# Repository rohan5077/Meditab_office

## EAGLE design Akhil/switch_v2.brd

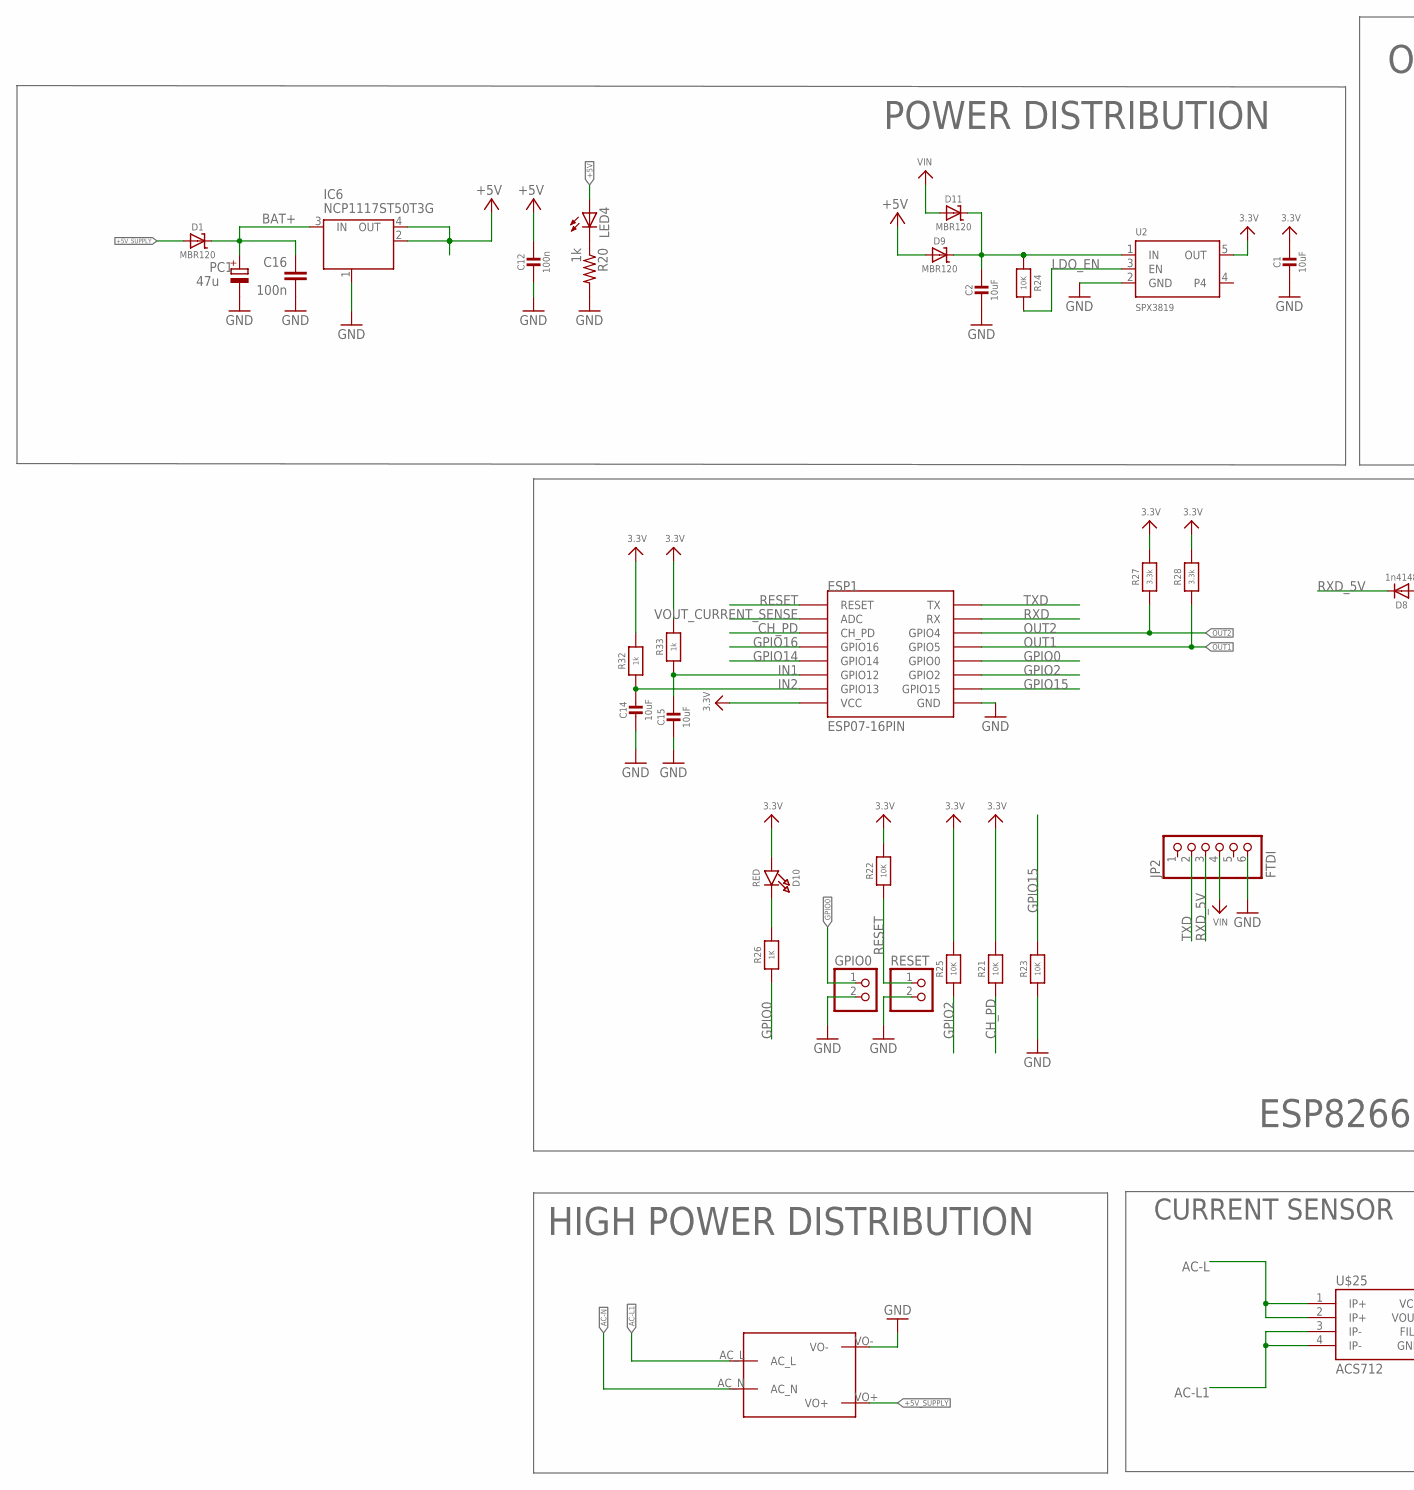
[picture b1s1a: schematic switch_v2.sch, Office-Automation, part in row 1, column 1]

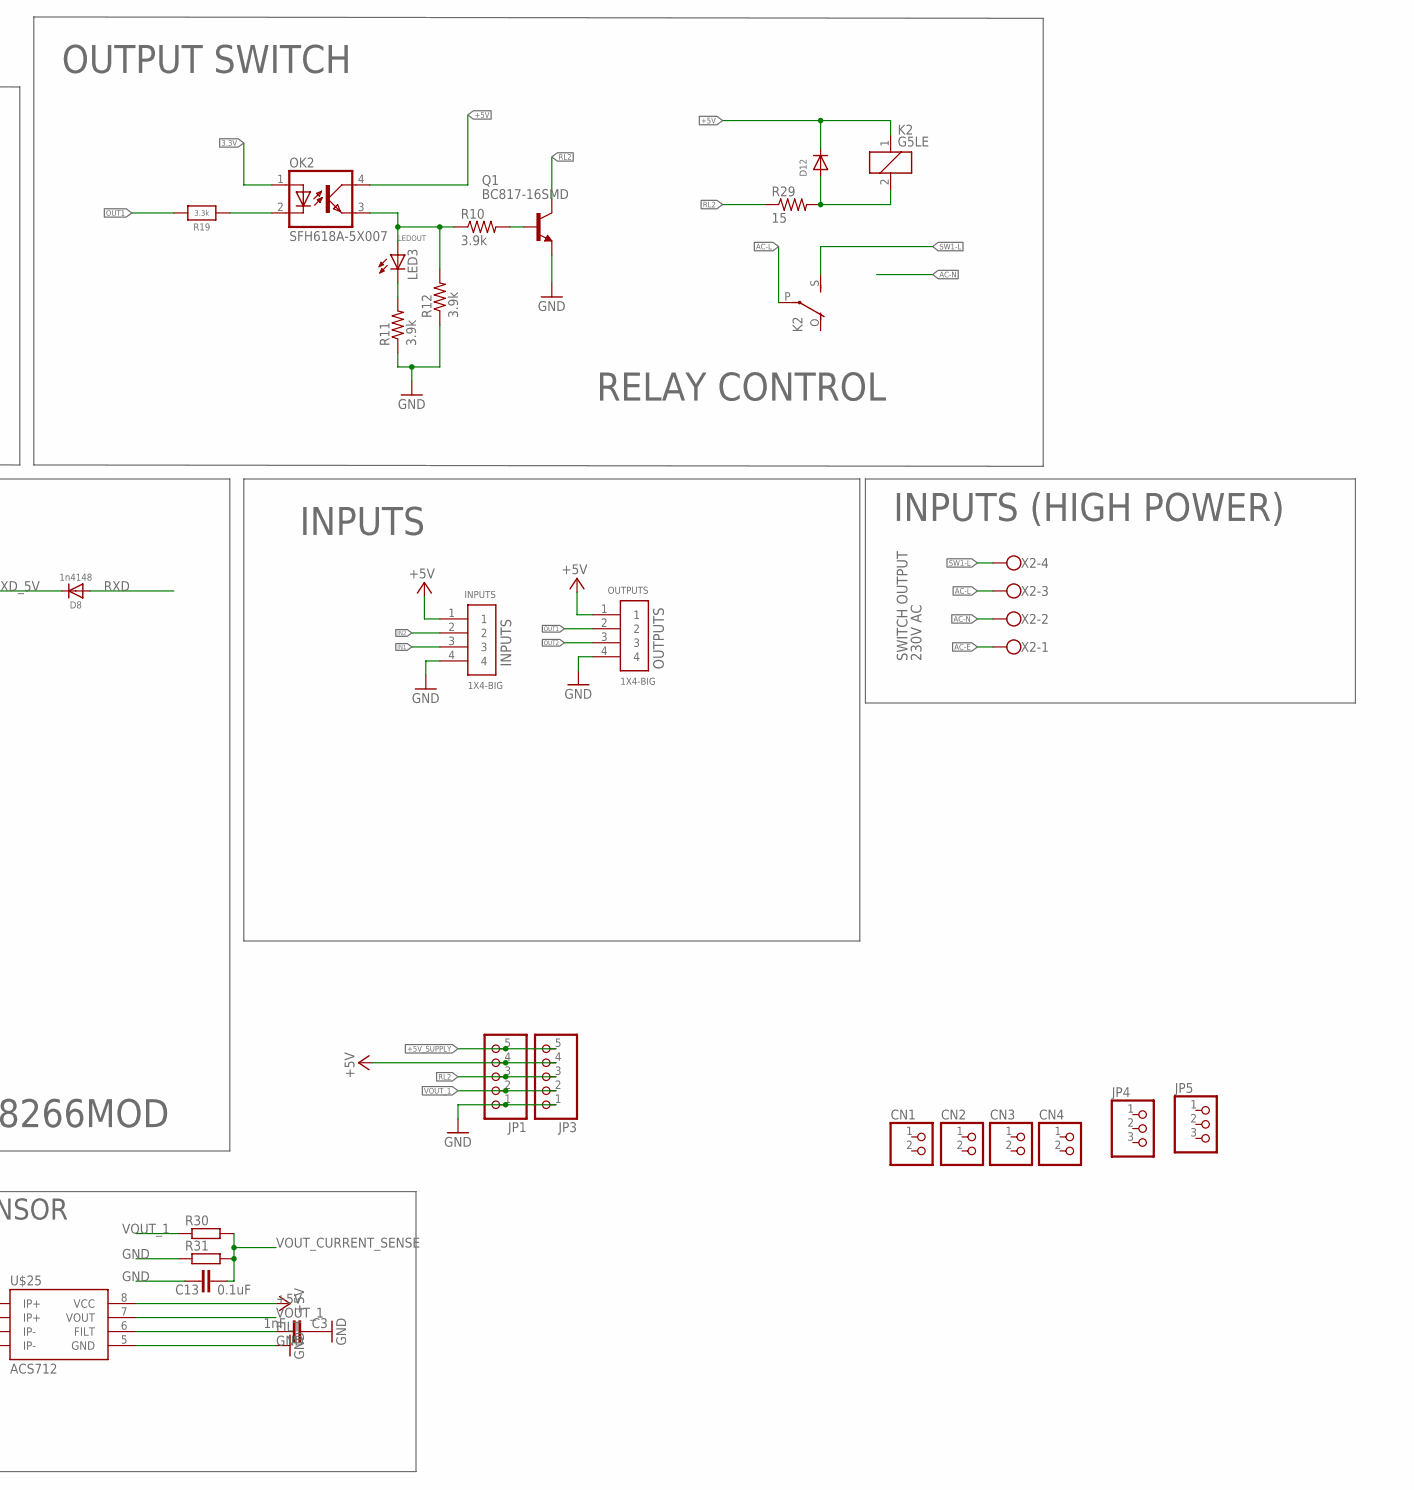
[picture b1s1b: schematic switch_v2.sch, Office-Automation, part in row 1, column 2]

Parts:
C1, C2, C14, C15: 10uF; _0603
C3: 1nF; C0603-ROUND
C12: 100n; _0603
C13: 0.1uF; C0603-ROUND
C16: 100n; C0603-ROUND
CN1, CN2, CN3, CN4: PINHD-1X2; 1X02
D1, D9, D11: MBR120; SOD-123
D8: 1n4148; SOD-323
D10: RED; CHIPLED_0603_NOOUTLINE
D12: DIODESOD-523; SOD-523
ESP1: ESP07-16PIN
GPIO0: PINHD-1X2; 1X02
IC6: NCP1117ST50T3G; SOT223
INPUTS: 1X4-BIG; 1X04-BIG
JP1, JP3: PINHD-1X5; 1X05
JP2: FTDI; 1X06_ROUND_70
JP4, JP5: PINHD-1X3; 1X03
K2: G5LE
LED3, LED4: LEDCHIP-LED0603; CHIP-LED0603
OK2: SFH618A-5X007; SMD4-7
OUTPUTS: 1X4-BIG; 1X04-BIG
PC1: 47u; PANASONIC_D
Q1: BC817-16SMD; SOT23-BEC
R10, R11, R12: 3.9k; R0603
R19: 3.3k; _0603MP
R20: 1k; R0603
R21, R22, R23, R24, R25: 10K; 0603-NO
R26: 1K; 0603-NO
R27, R28: 3.3k; _0603
R29: 15; R0603
R30, R31: R-EU_R0603; R0603
R32, R33: 1k; _0603
RESET: PINHD-1X2; 1X02
U2: SPX3819; SOT23-5
U$24: MAINS_CONVERTERS; HLK-PM01
U$25: ACS712; SO08
X2: W237-4

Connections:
3.3V: C1.1, D10.A, ESP1.VCC, OK2.1 (A), R21.2, R22.2, R25.2, R27.2, R28.2, R32.2, R33.2, U2.5 (OUT)
+5V: C12.1, D9.A, D12.K (C), IC6.2 (OUT), IC6.4 (OUT), INPUTS.1, JP1.4, JP3.4, K2.1, LED4.A, OK2.4 (COL), OUTPUTS.1, U$25.8 (VCC)
+5V_SUPPLY: D1.A, JP1.5, JP3.5, U$24.VO+
AC-E: X2.1
AC-L: K2.P, U$25.1 (IP+), U$25.2 (IP+), X2.3
AC-L1: U$24.AC_L, U$25.3 (IP-), U$25.4 (IP-)
AC-N: U$24.AC_N, X2.2
BAT+: C16.1, D1.C, IC6.3 (IN), PC1.+
CH_PD: ESP1.CH_PD, R21.1
FILT: C3.2, U$25.6 (FILT)
GND: C1.2, C2.2, C3.1, C12.2, C13.1, C14.2, C15.2, C16.2, ESP1.GND, GPIO0.2, IC6.1 (GND/ADJ), INPUTS.4, JP1.1, JP2.6, JP3.1, OUTPUTS.4, PC1.-, Q1.E, R11.1, R12.1, R20.2, R23.1, R31.1, RESET.2, U2.2 (GND), U$24.VO-, U$25.5 (GND)
GPIO0: ESP1.GPIO0, GPIO0.1, R26.1
GPIO2: ESP1.GPIO2, R25.1
GPIO14: ESP1.GPIO14
GPIO15: ESP1.GPIO15, R23.2
GPIO16: ESP1.GPIO16
IN1: C15.1, ESP1.GPIO12, INPUTS.3, R33.1
IN2: C14.1, ESP1.GPIO13, INPUTS.2, R32.1
LDO_EN: R24.2, U2.3 (EN)
LEDOUT: LED3.A, OK2.3 (EMIT), R10.1, R12.2
unnamed: LED4.C, R20.1
unnamed: C2.1, D9.C, D11.C, R24.1, U2.1 (IN)
unnamed: D10.C, R26.2
unnamed: Q1.B, R10.2
unnamed: LED3.C, R11.2
unnamed: OK2.2 (C), R19.1
unnamed: D12.A, K2.2, R29.2
OUT1: ESP1.GPIO5, OUTPUTS.2, R19.2, R28.1
OUT2: ESP1.GPIO4, OUTPUTS.3, R27.1
RESET: ESP1.REST (RESET), R22.1, RESET.1
RL2: JP1.3, JP3.3, Q1.C, R29.1
RXD: D8.A, ESP1.RX
RXD_5V: D8.C, JP2.3
SW1-L: K2.S, X2.4
TXD: ESP1.TX, JP2.2
VIN5V: D11.A, JP2.4
VOUT_1: JP1.2, JP3.2, R30.1, U$25.7 (VOUT)
VOUT_CURRENT_SENSE: C13.2, ESP1.ADC, R30.2, R31.2

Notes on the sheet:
INPUTS
POWER DISTRIBUTION
ESP8266MOD
OUTPUT SWITCH
HIGH POWER DISTRIBUTION
230V AC
SWITCH OUTPUT
INPUTS (HIGH POWER)
RELAY CONTROL
CURRENT SENSOR
OUTPUTS

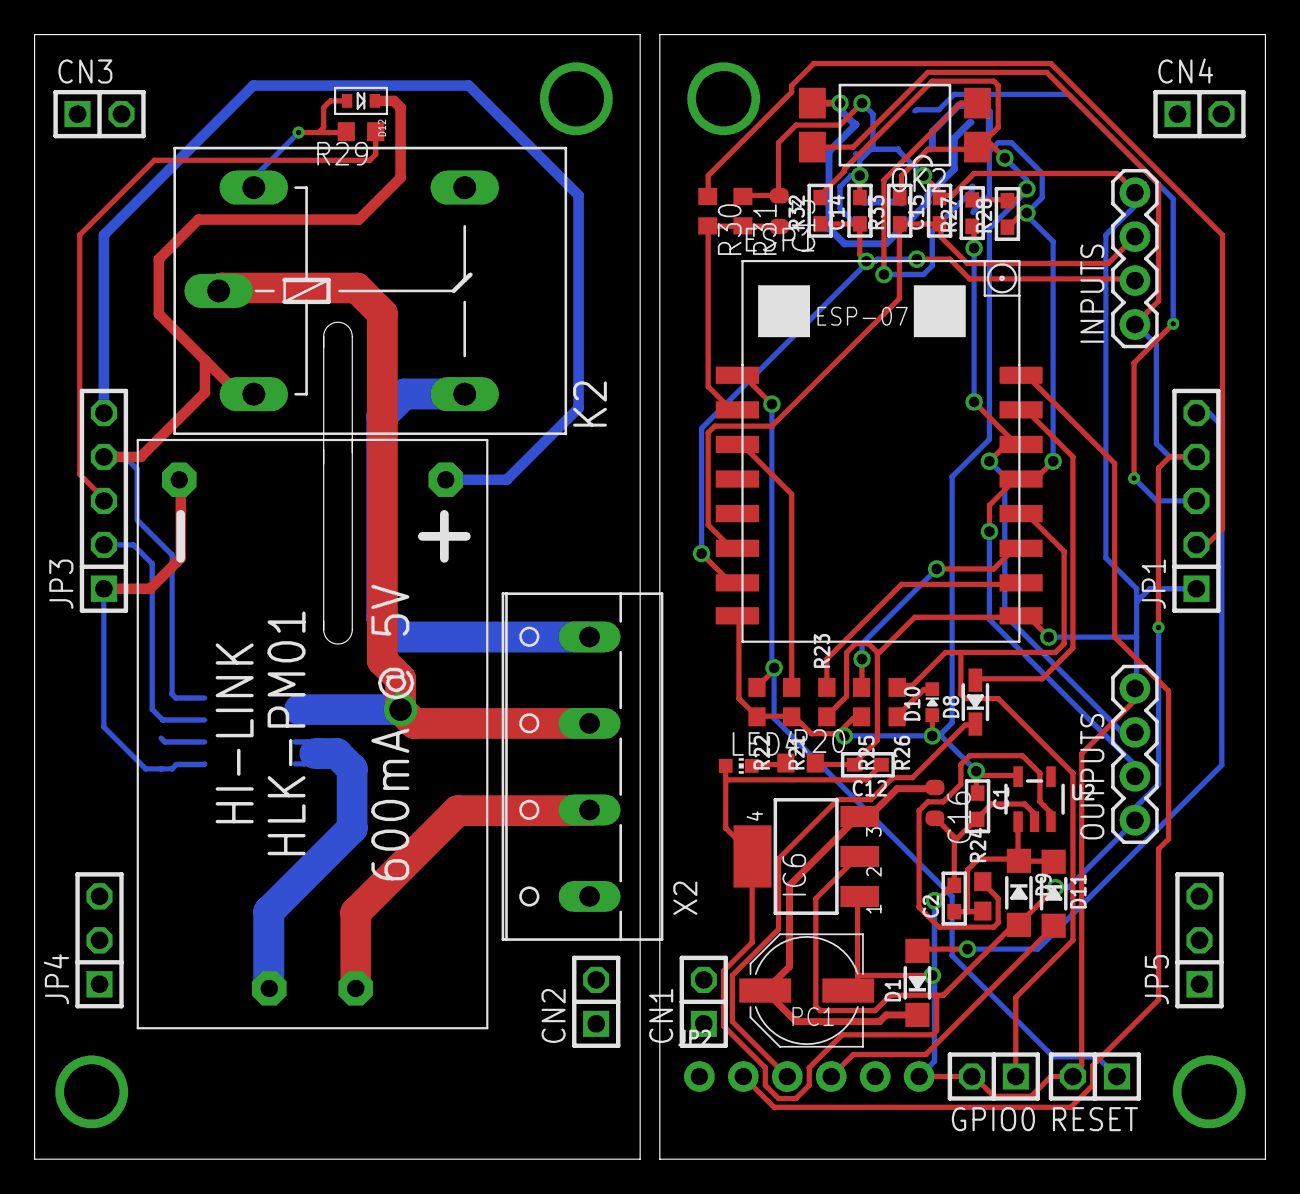
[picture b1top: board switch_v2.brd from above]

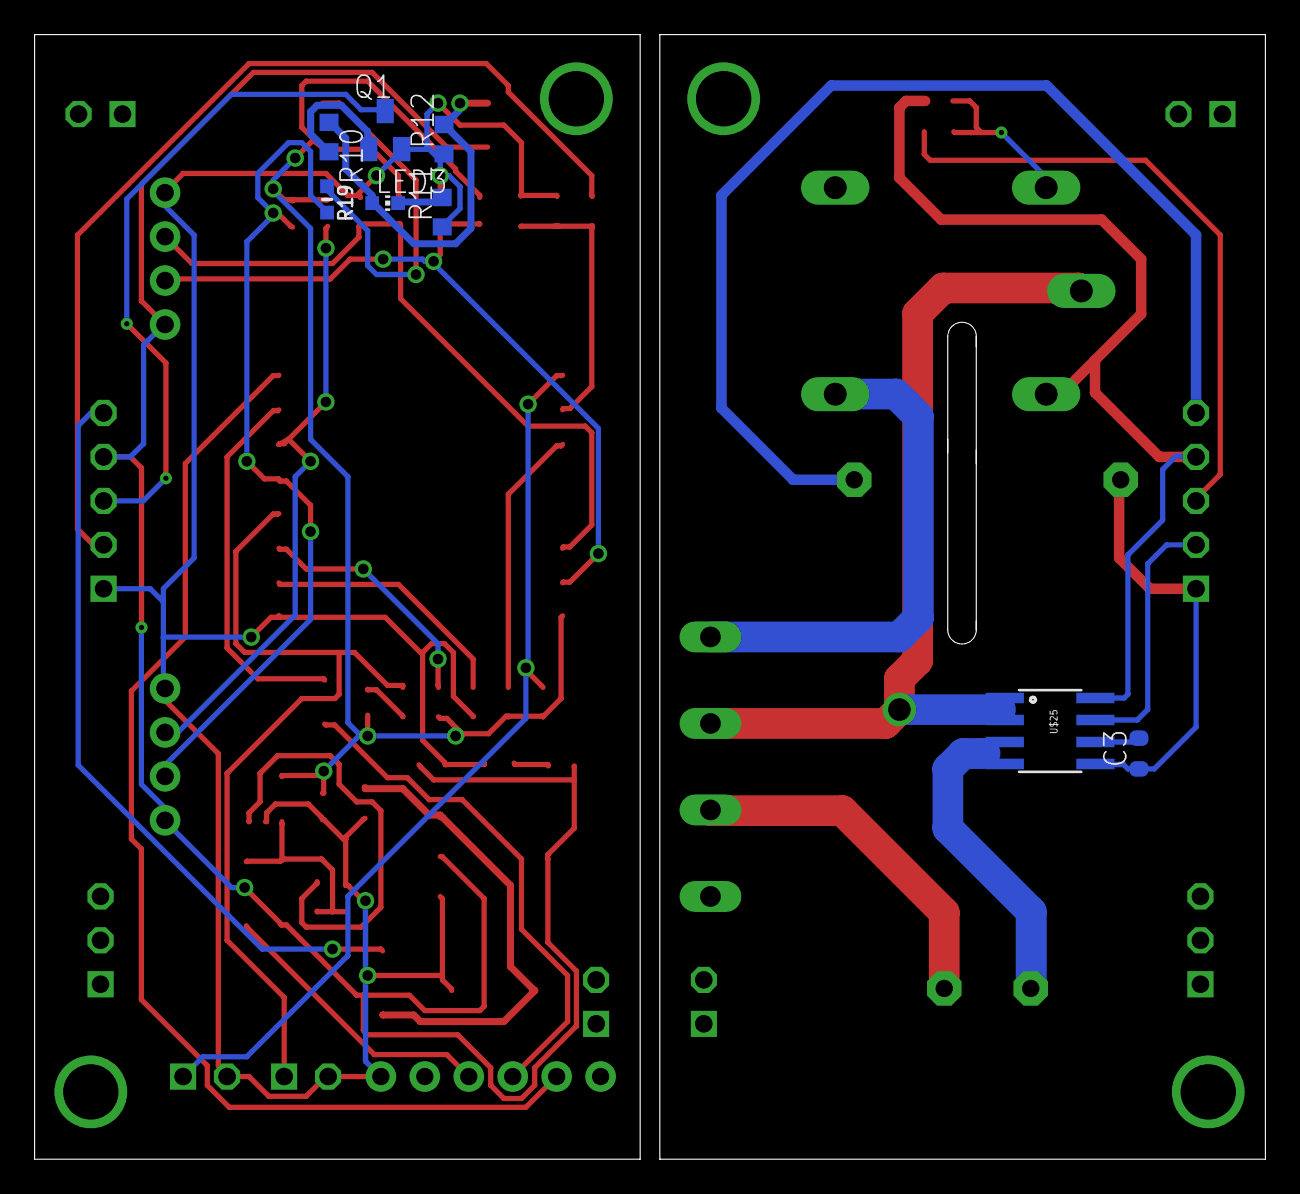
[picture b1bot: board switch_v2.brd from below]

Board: 2 copper layers, 71.1 x 65.0 mm, 57 parts (8 on the bottom side), 35 nets.

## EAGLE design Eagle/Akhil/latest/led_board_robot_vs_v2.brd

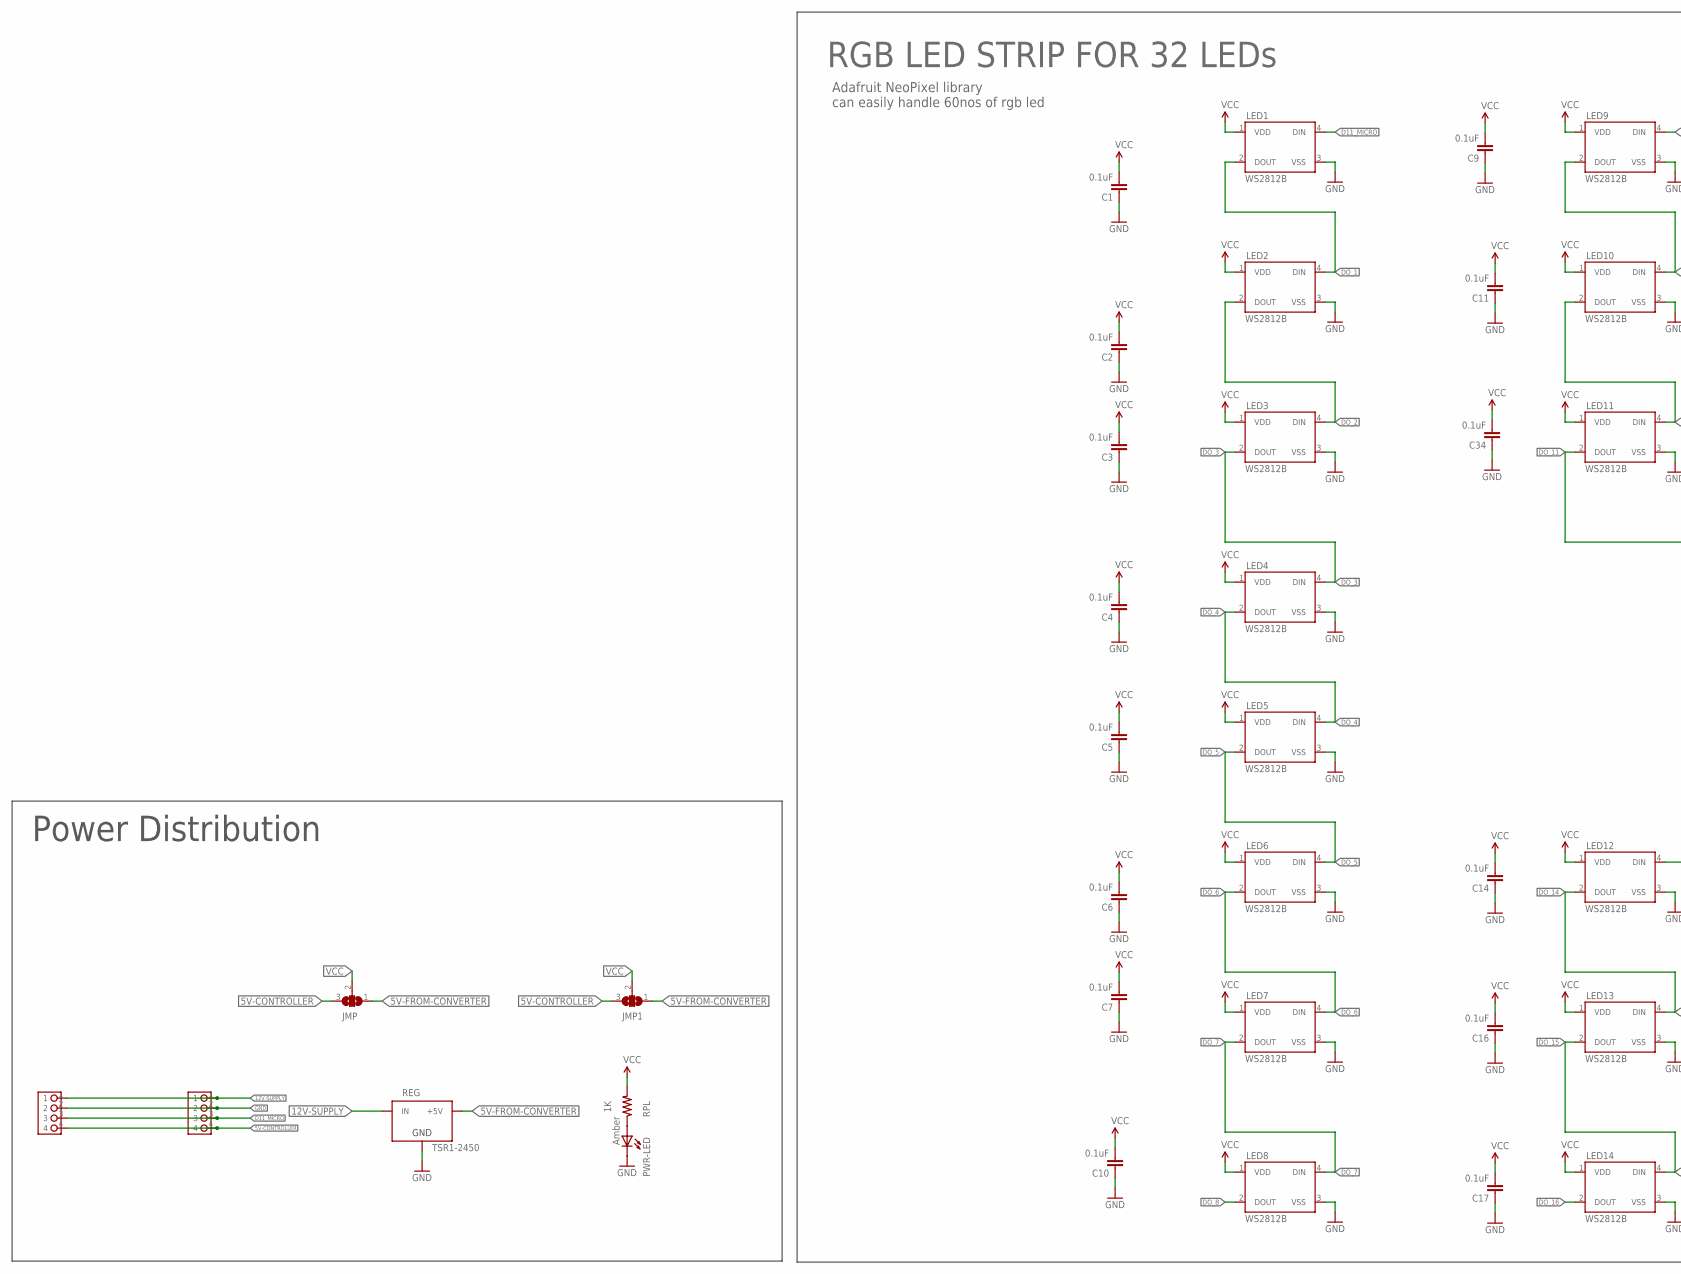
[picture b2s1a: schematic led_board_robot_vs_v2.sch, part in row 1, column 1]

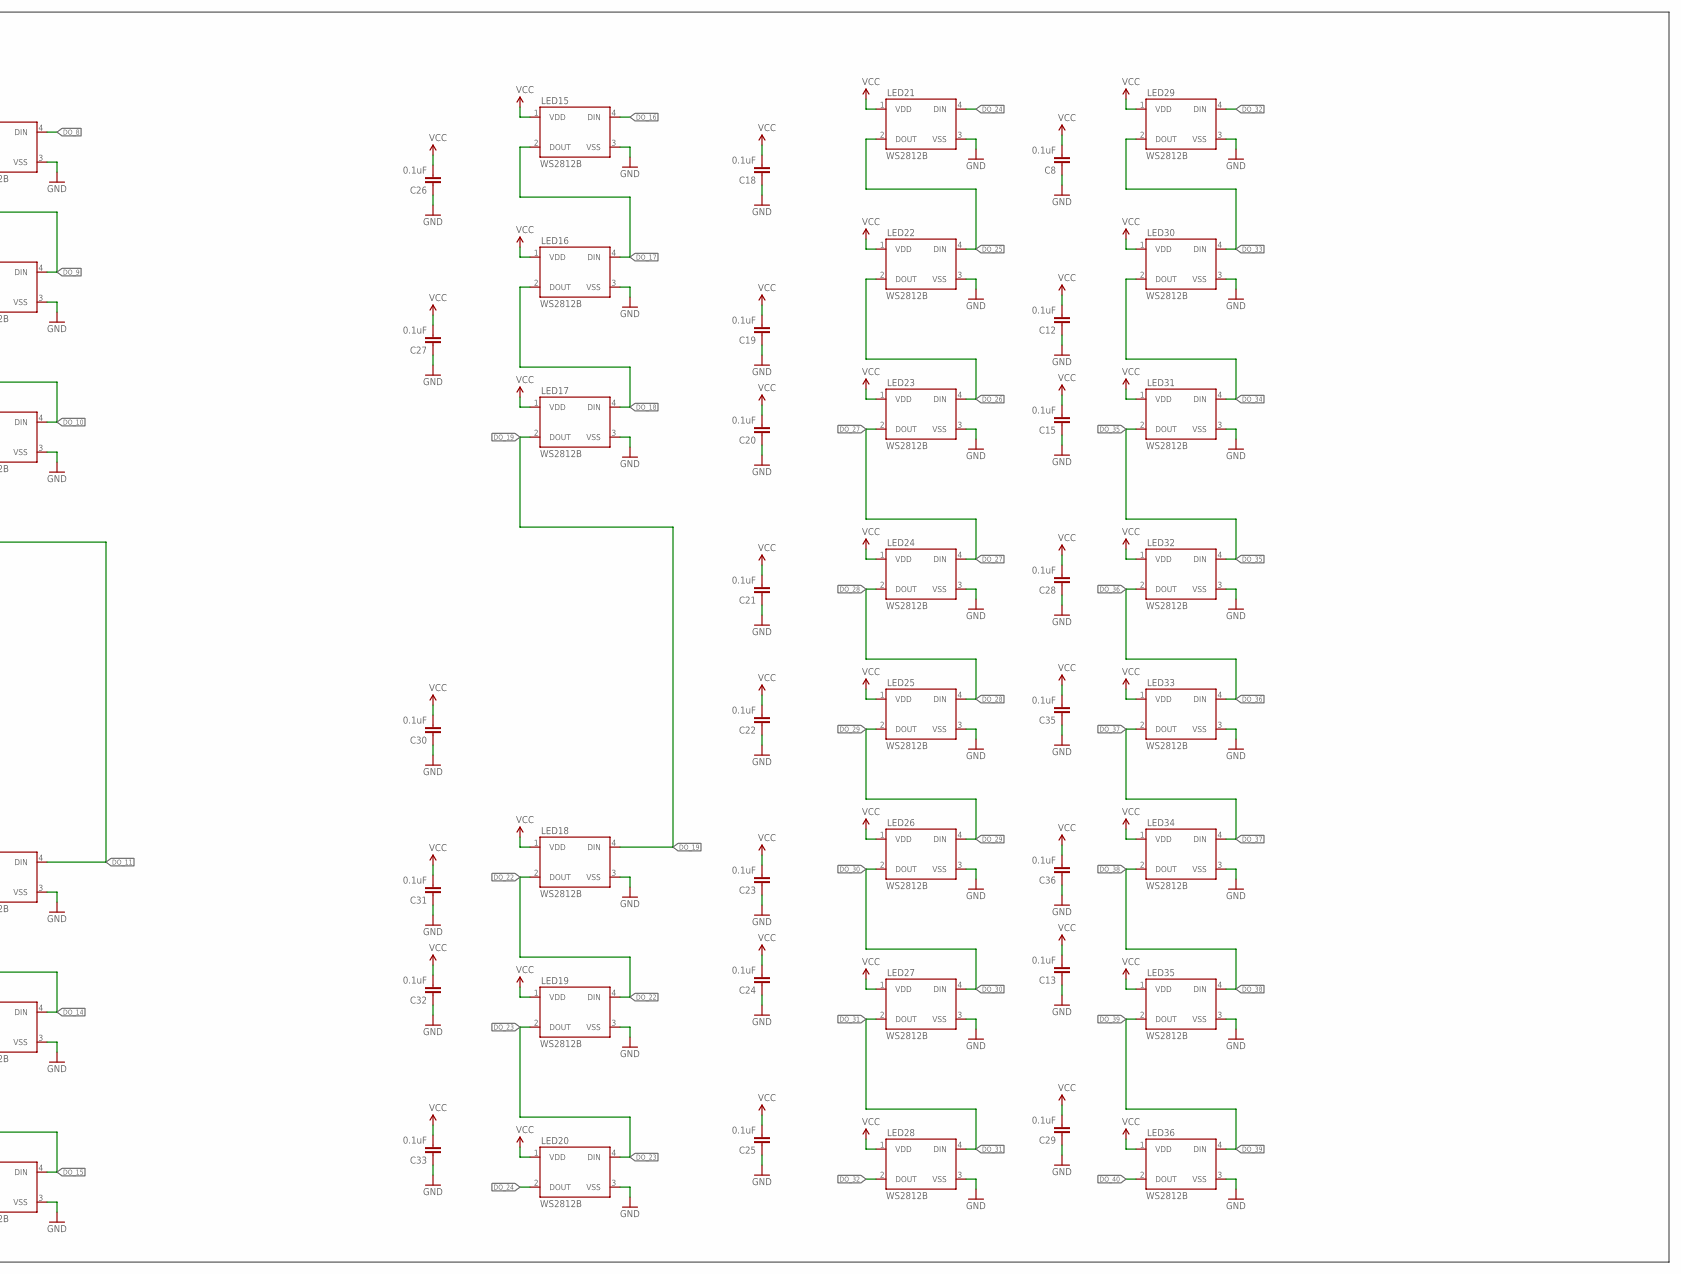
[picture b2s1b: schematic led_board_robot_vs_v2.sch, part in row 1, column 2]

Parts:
C1, C2, C3, C4, C5, C6, C7, C8, C9, C10, C11, C12, C13, C14, C15, C16, C17, C18, C19, C20, C21, C22, C23, C24, C25, C26, C27, C28, C29, C30, C31, C32, C33, C34, C35, C36: 0.1uF; 0603-CAP
CON1, CON2: MOLEX_LOCKING_4PIN
JMP, JMP1: SJ2WW; SJ_2W
LED1, LED2, LED3, LED4, LED5, LED6, LED7, LED8, LED9, LED10, LED11, LED12, LED13, LED14, LED15, LED16, LED17, LED18, LED19, LED20, LED21, LED22, LED23, LED24, LED25, LED26, LED27, LED28, LED29, LED30, LED31, LED32, LED33, LED34, LED35, LED36: WS2812B
PWR-LED: Amber; LED-0603
REG: TSR1-2450; TSR-1
RPL: 1K; 0603-RES

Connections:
5V-CONTROLLER: CON1.4, CON2.4, JMP.3, JMP1.3
5V-FROM-CONVERTER: JMP.1, JMP1.1, REG.3 (+5V)
12V-SUPPLY: CON1.1, CON2.1, REG.1 (IN)
D11_MICRO: CON1.3, CON2.3, LED1.4 (DIN)
DO_1: LED1.2 (DOUT), LED2.4 (DIN)
DO_2: LED2.2 (DOUT), LED3.4 (DIN)
DO_3: LED3.2 (DOUT), LED4.4 (DIN)
DO_4: LED4.2 (DOUT), LED5.4 (DIN)
DO_5: LED5.2 (DOUT), LED6.4 (DIN)
DO_6: LED6.2 (DOUT), LED7.4 (DIN)
DO_7: LED7.2 (DOUT), LED8.4 (DIN)
DO_8: LED8.2 (DOUT), LED9.4 (DIN)
DO_9: LED9.2 (DOUT), LED10.4 (DIN)
DO_10: LED10.2 (DOUT), LED11.4 (DIN)
DO_11: LED11.2 (DOUT), LED12.4 (DIN)
DO_14: LED12.2 (DOUT), LED13.4 (DIN)
DO_15: LED13.2 (DOUT), LED14.4 (DIN)
DO_16: LED14.2 (DOUT), LED15.4 (DIN)
DO_17: LED15.2 (DOUT), LED16.4 (DIN)
DO_18: LED16.2 (DOUT), LED17.4 (DIN)
DO_19: LED17.2 (DOUT), LED18.4 (DIN)
DO_22: LED18.2 (DOUT), LED19.4 (DIN)
DO_23: LED19.2 (DOUT), LED20.4 (DIN)
DO_24: LED20.2 (DOUT), LED21.4 (DIN)
DO_25: LED21.2 (DOUT), LED22.4 (DIN)
DO_26: LED22.2 (DOUT), LED23.4 (DIN)
DO_27: LED23.2 (DOUT), LED24.4 (DIN)
DO_28: LED24.2 (DOUT), LED25.4 (DIN)
DO_29: LED25.2 (DOUT), LED26.4 (DIN)
DO_30: LED26.2 (DOUT), LED27.4 (DIN)
DO_31: LED27.2 (DOUT), LED28.4 (DIN)
DO_32: LED28.2 (DOUT), LED29.4 (DIN)
DO_33: LED29.2 (DOUT), LED30.4 (DIN)
DO_34: LED30.2 (DOUT), LED31.4 (DIN)
DO_35: LED31.2 (DOUT), LED32.4 (DIN)
DO_36: LED32.2 (DOUT), LED33.4 (DIN)
DO_37: LED33.2 (DOUT), LED34.4 (DIN)
DO_38: LED34.2 (DOUT), LED35.4 (DIN)
DO_39: LED35.2 (DOUT), LED36.4 (DIN)
DO_40: LED36.2 (DOUT)
GND: C1.1, C2.1, C3.1, C4.1, C5.1, C6.1, C7.1, C8.1, C9.1, C10.1, C11.1, C12.1, C13.1, C14.1, C15.1, C16.1, C17.1, C18.1, C19.1, C20.1, C21.1, C22.1, C23.1, C24.1, C25.1, C26.1, C27.1, C28.1, C29.1, C30.1, C31.1, C32.1, C33.1, C34.1, C35.1, C36.1, CON1.2, CON2.2, LED1.3 (VSS), LED2.3 (VSS), LED3.3 (VSS), LED4.3 (VSS), LED5.3 (VSS), LED6.3 (VSS), LED7.3 (VSS), LED8.3 (VSS), LED9.3 (VSS), LED10.3 (VSS), LED11.3 (VSS), LED12.3 (VSS), LED13.3 (VSS), LED14.3 (VSS), LED15.3 (VSS), LED16.3 (VSS), LED17.3 (VSS), LED18.3 (VSS), LED19.3 (VSS), LED20.3 (VSS), LED21.3 (VSS), LED22.3 (VSS), LED23.3 (VSS), LED24.3 (VSS), LED25.3 (VSS), LED26.3 (VSS), LED27.3 (VSS), LED28.3 (VSS), LED29.3 (VSS), LED30.3 (VSS), LED31.3 (VSS), LED32.3 (VSS), LED33.3 (VSS), LED34.3 (VSS), LED35.3 (VSS), LED36.3 (VSS), PWR-LED.C, REG.2 (GND)
unnamed: PWR-LED.A, RPL.1
VCC: C1.2, C2.2, C3.2, C4.2, C5.2, C6.2, C7.2, C8.2, C9.2, C10.2, C11.2, C12.2, C13.2, C14.2, C15.2, C16.2, C17.2, C18.2, C19.2, C20.2, C21.2, C22.2, C23.2, C24.2, C25.2, C26.2, C27.2, C28.2, C29.2, C30.2, C31.2, C32.2, C33.2, C34.2, C35.2, C36.2, JMP.2, JMP1.2, LED1.1 (VDD), LED2.1 (VDD), LED3.1 (VDD), LED4.1 (VDD), LED5.1 (VDD), LED6.1 (VDD), LED7.1 (VDD), LED8.1 (VDD), LED9.1 (VDD), LED10.1 (VDD), LED11.1 (VDD), LED12.1 (VDD), LED13.1 (VDD), LED14.1 (VDD), LED15.1 (VDD), LED16.1 (VDD), LED17.1 (VDD), LED18.1 (VDD), LED19.1 (VDD), LED20.1 (VDD), LED21.1 (VDD), LED22.1 (VDD), LED23.1 (VDD), LED24.1 (VDD), LED25.1 (VDD), LED26.1 (VDD), LED27.1 (VDD), LED28.1 (VDD), LED29.1 (VDD), LED30.1 (VDD), LED31.1 (VDD), LED32.1 (VDD), LED33.1 (VDD), LED34.1 (VDD), LED35.1 (VDD), LED36.1 (VDD), RPL.2

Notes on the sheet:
Adafruit NeoPixel library can easily handle 60nos of rgb led
RGB LED STRIP FOR 32 LEDs
Power Distribution

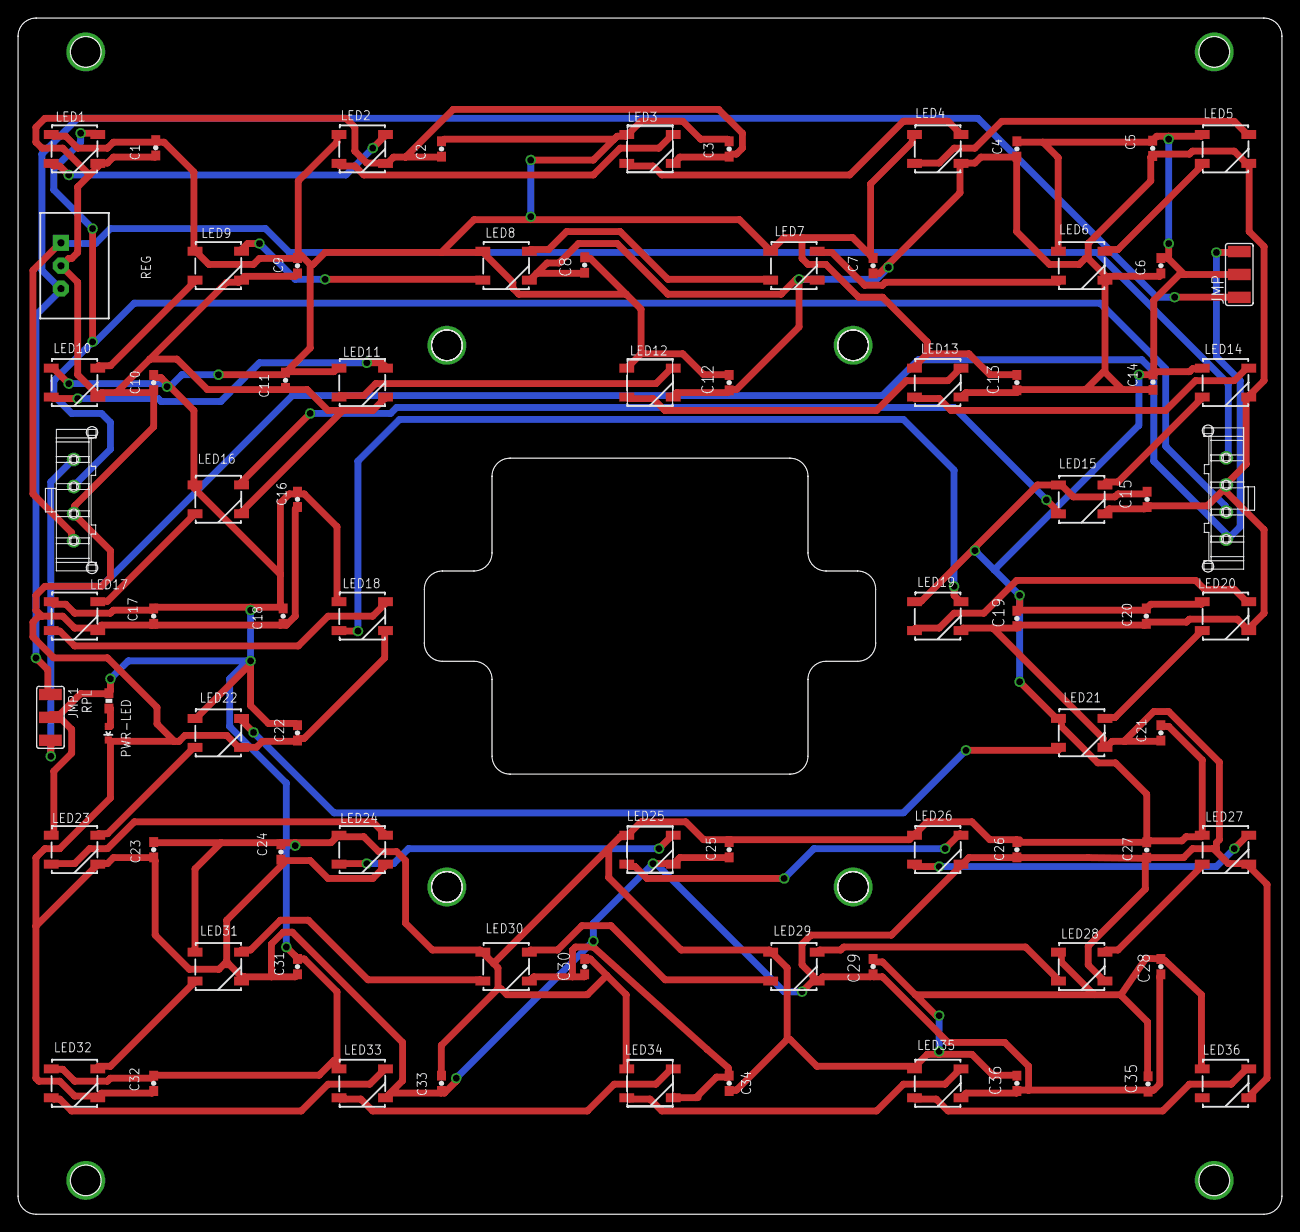
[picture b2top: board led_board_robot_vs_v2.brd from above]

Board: 2 copper layers, 140.0 x 132.5 mm, 79 parts (0 on the bottom side), 42 nets.

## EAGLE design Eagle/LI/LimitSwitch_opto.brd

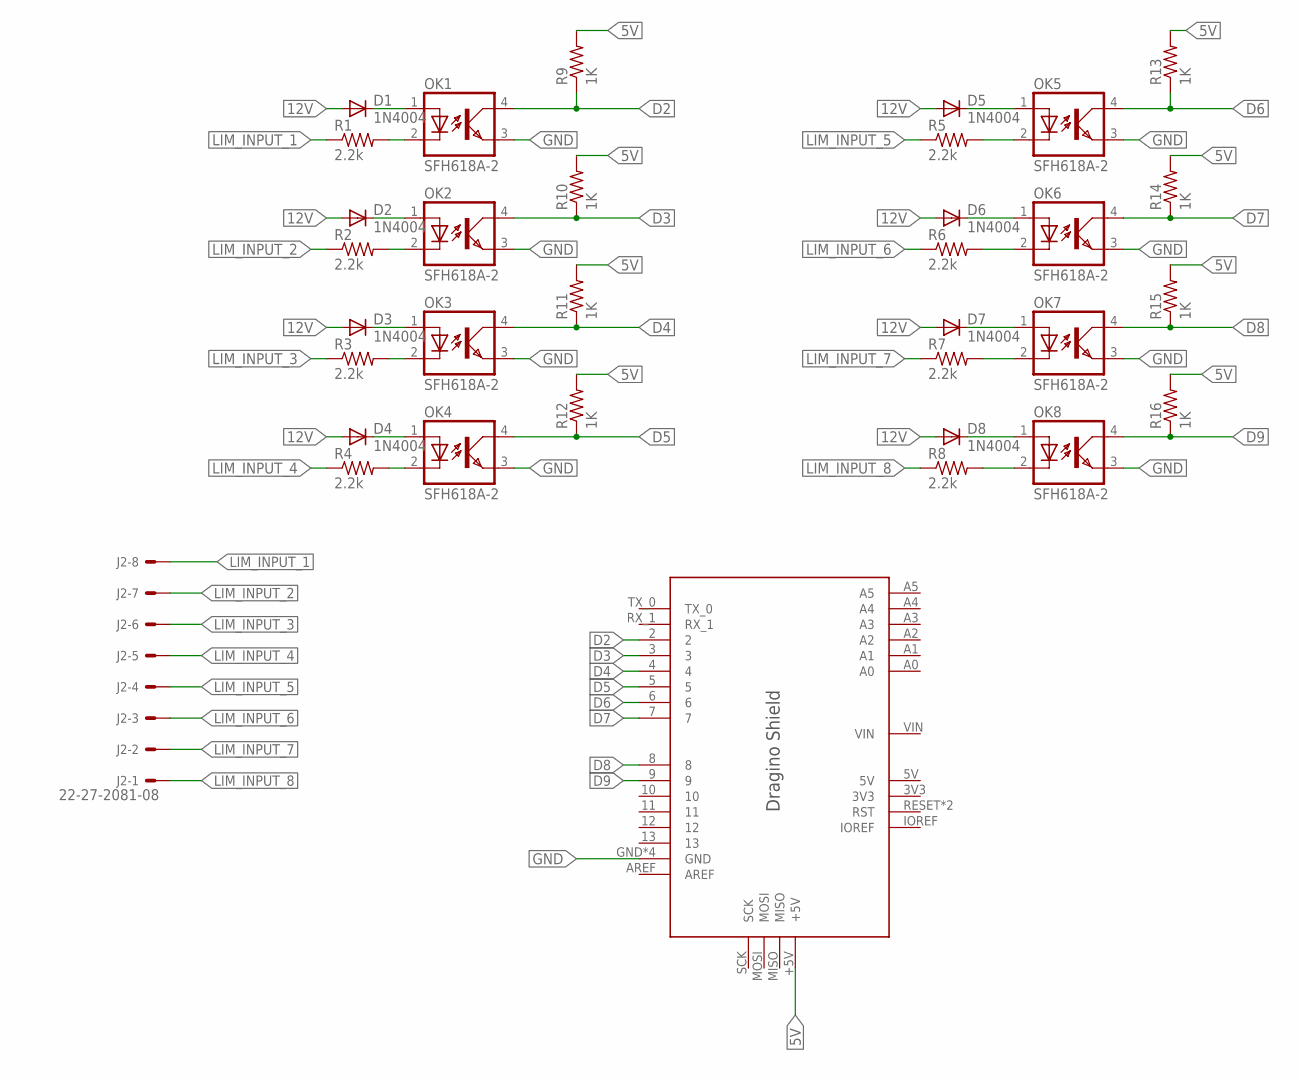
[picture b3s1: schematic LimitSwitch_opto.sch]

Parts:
D1, D2, D3, D4, D5, D6, D7, D8: 1N4004; DO41-10
J2: 22-27-2081-08; 6410-08
OK1, OK2, OK3, OK4, OK5, OK6, OK7, OK8: SFH618A-2; DIP4
R1, R2, R3, R4, R5, R6, R7, R8: 2.2k; 0204V
R9, R10, R11, R12, R13, R14, R15, R16: 1K; 0204V
U$1: DRAGINO_SHIELD

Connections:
5V: R9.2, R10.2, R11.2, R12.2, R13.2, R14.2, R15.2, R16.2, U$1.+5V
12V: D1.A, D2.A, D3.A, D4.A, D5.A, D6.A, D7.A, D8.A
D2: OK1.4 (COL), R9.1, U$1.2
D3: OK2.4 (COL), R10.1, U$1.3
D4: OK3.4 (COL), R11.1, U$1.4
D5: OK4.4 (COL), R12.1, U$1.5
D6: OK5.4 (COL), R13.1, U$1.6
D7: OK6.4 (COL), R14.1, U$1.7
D8: OK7.4 (COL), R15.1, U$1.8
D9: OK8.4 (COL), R16.1, U$1.9
GND: OK1.3 (EMIT), OK2.3 (EMIT), OK3.3 (EMIT), OK4.3 (EMIT), OK5.3 (EMIT), OK6.3 (EMIT), OK7.3 (EMIT), OK8.3 (EMIT), U$1.GND, U$1.GND@1 (GND), U$1.GND@2 (GND), U$1.GND@3 (GND)
LIM_INPUT_1: R1.1
LIM_INPUT_2: R2.1
LIM_INPUT_3: R3.1
LIM_INPUT_4: R4.1
LIM_INPUT_5: R5.1
LIM_INPUT_6: R6.1
LIM_INPUT_7: R7.1
LIM_INPUT_8: R8.1
unnamed: D1.C, OK1.1 (A)
unnamed: D2.C, OK2.1 (A)
unnamed: D3.C, OK3.1 (A)
unnamed: D4.C, OK4.1 (A)
unnamed: D8.C, OK8.1 (A)
unnamed: D7.C, OK7.1 (A)
unnamed: D6.C, OK6.1 (A)
unnamed: D5.C, OK5.1 (A)
unnamed: OK1.2 (C), R1.2
unnamed: OK2.2 (C), R2.2
unnamed: OK3.2 (C), R3.2
unnamed: OK4.2 (C), R4.2
unnamed: OK5.2 (C), R5.2
unnamed: OK6.2 (C), R6.2
unnamed: OK7.2 (C), R7.2
unnamed: OK8.2 (C), R8.2

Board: 2 copper layers, 34 parts (0 on the bottom side), 27 nets, no tracks yet.

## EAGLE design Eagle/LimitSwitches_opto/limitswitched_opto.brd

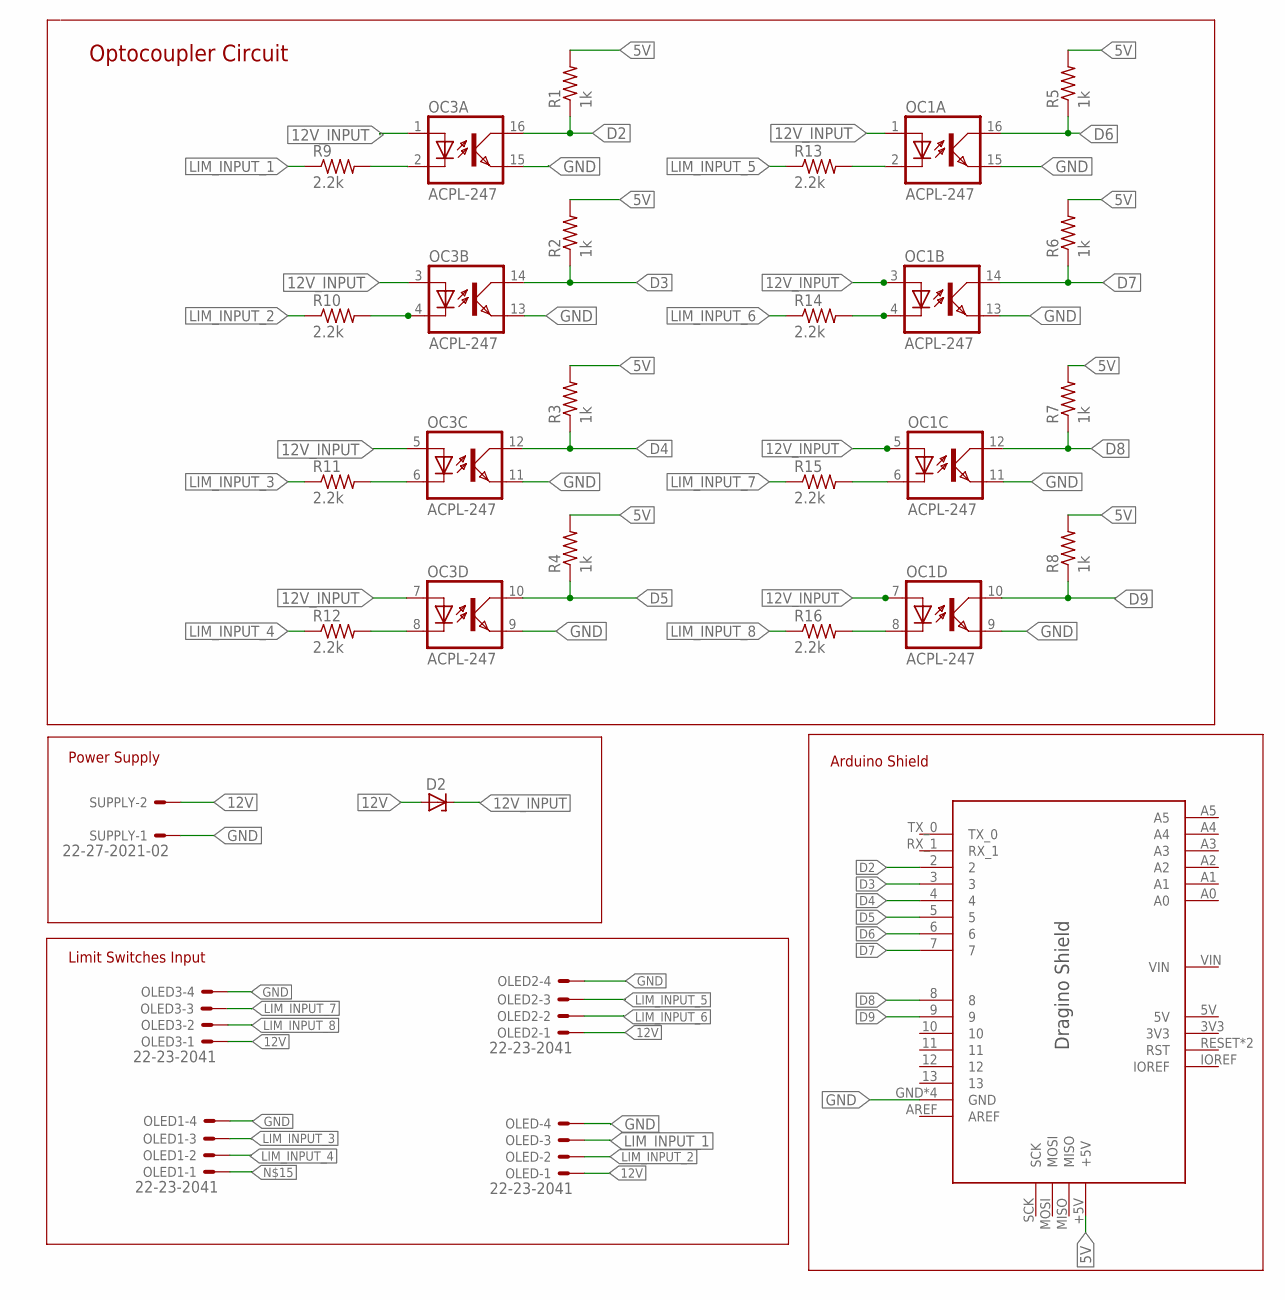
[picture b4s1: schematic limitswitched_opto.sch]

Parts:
D2: 1SMA5925BT3G; DO214AC
OC1, OC3: ACPL-247; SOP16
OLED, OLED1, OLED2, OLED3: 22-23-2041
R1, R2, R3, R4, R5, R6, R7, R8: 1k; R0603
R9, R10, R11, R12, R13, R14, R15, R16: 2.2k; R0603
SUPPLY: 22-27-2021-02; 6410-02
U$1: DRAGINO_SHIELD

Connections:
5V: R1.2, R2.2, R3.2, R4.2, R5.2, R6.2, R7.2, R8.2, U$1.+5V
12V: D2.A, OLED.1, OLED2.1, OLED3.1, SUPPLY.2
12V_INPUT: D2.C, OC1.1 (A), OC1.3 (A), OC1.5 (A), OC1.7 (A), OC3.1 (A), OC3.3 (A), OC3.5 (A), OC3.7 (A)
D2: OC3.16 (COL), R1.1, U$1.2
D3: OC3.14 (COL), R2.1, U$1.3
D4: OC3.12 (COL), R3.1, U$1.4
D5: OC3.10 (COL), R4.1, U$1.5
D6: OC1.16 (COL), R5.1, U$1.6
D7: OC1.14 (COL), R6.1, U$1.7
D8: OC1.12 (COL), R7.1, U$1.8
D9: OC1.10 (COL), R8.1, U$1.9
GND: OC1.9 (EMIT), OC1.11 (EMIT), OC1.13 (EMIT), OC1.15 (EMIT), OC3.9 (EMIT), OC3.11 (EMIT), OC3.13 (EMIT), OC3.15 (EMIT), OLED.4, OLED1.4, OLED2.4, OLED3.4, SUPPLY.1, U$1.GND, U$1.GND@1 (GND), U$1.GND@2 (GND), U$1.GND@3 (GND)
LIM_INPUT_1: OLED.3, R9.1
LIM_INPUT_2: OLED.2, R10.1
LIM_INPUT_3: OLED1.3, R11.1
LIM_INPUT_4: OLED1.2, R12.1
LIM_INPUT_5: OLED2.3, R13.1
LIM_INPUT_6: OLED2.2, R14.1
LIM_INPUT_7: OLED3.3, R15.1
LIM_INPUT_8: OLED3.2, R16.1
unnamed: OC1.2 (C), R13.2
unnamed: OC1.4 (C), R14.2
unnamed: OC1.6 (C), R15.2
unnamed: OC1.8 (C), R16.2
unnamed: OC3.6 (C), R11.2
unnamed: OC3.8 (C), R12.2
unnamed: OC3.2 (C), R9.2
unnamed: OC3.4 (C), R10.2

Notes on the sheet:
Optocoupler Circuit
Limit Switches Input
Power Supply
Arduino Shield

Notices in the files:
parts and their libraries:
microbuilder: This work is placed in the public domain, and may be freely used for commercial and non-commercial work with the following conditions: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
SparkFun-LED: Licensing: CC v3.0 Share-Alike You are welcome to use this library for commercial purposes.
